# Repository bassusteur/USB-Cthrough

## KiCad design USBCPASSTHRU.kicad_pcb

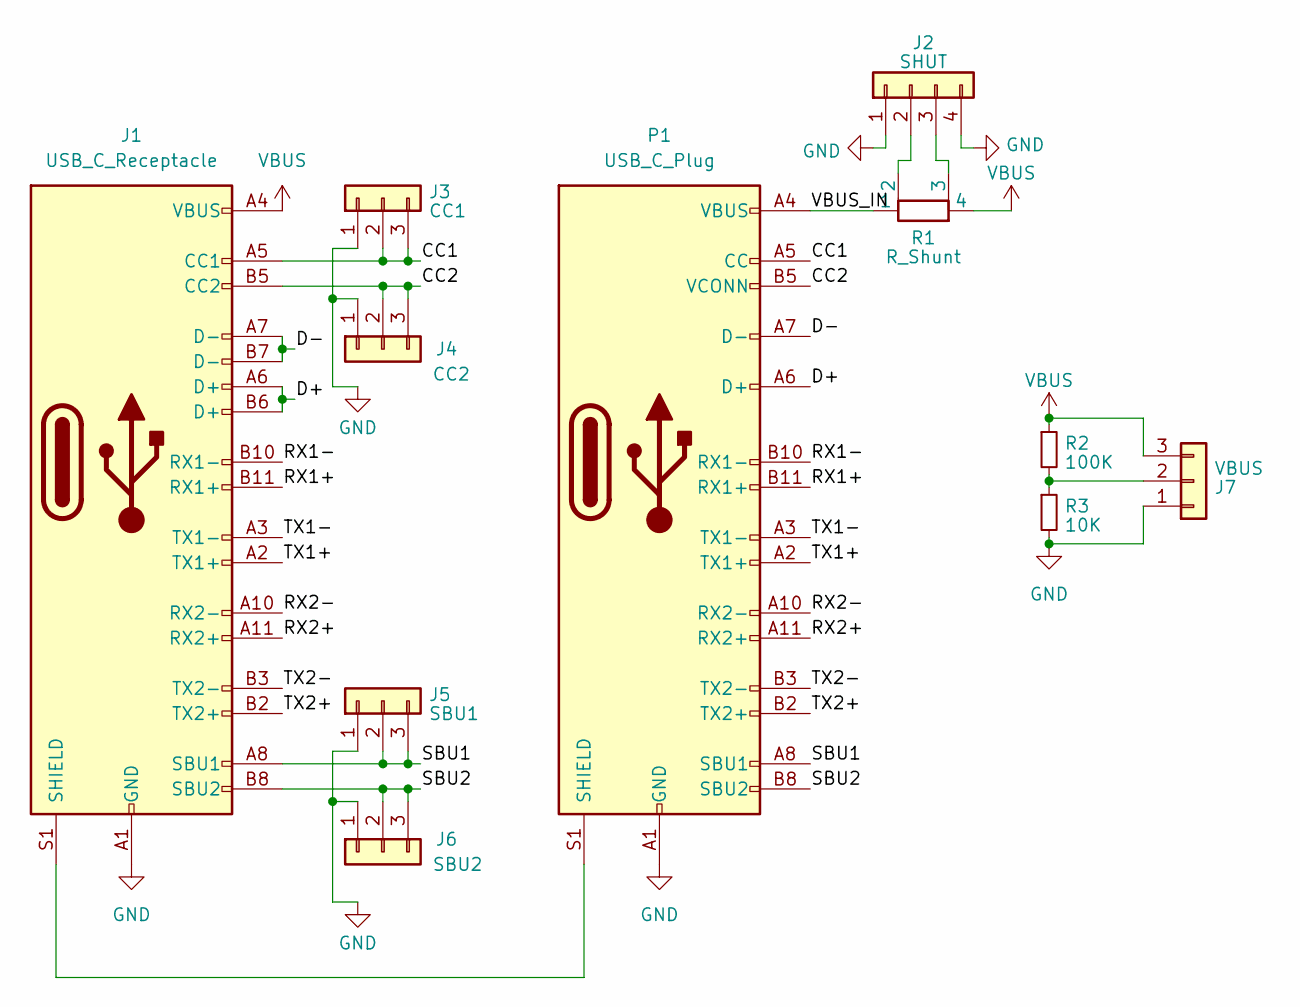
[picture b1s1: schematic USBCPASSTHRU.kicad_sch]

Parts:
J1: USB_C_Receptacle; USB_C_Receptacle_Amphenol_12401548E4-2A
J2: SHUT; PinHeader_1x04_P2.54mm_Vertical
J3: CC1; PinHeader_1x03_P2.54mm_Vertical
J4: CC2; PinHeader_1x03_P2.54mm_Vertical
J5: SBU1; PinHeader_1x03_P2.54mm_Vertical
J6: SBU2; PinHeader_1x03_P2.54mm_Vertical
J7: VBUS; PinHeader_1x03_P2.54mm_Vertical
P1: USB_C_Plug; USB_C_Plug_Molex_105444
R1: R_Shunt; Shunt
R2: 100K; R_0603_1608Metric
R3: 10K; R_0603_1608Metric

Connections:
/CC1: J1.A5 (CC1), J3.2, J3.3, P1.A5 (CC)
/CC2: J1.B5 (CC2), J4.2, J4.3, P1.B5 (VCONN)
/D+: J1.A6 (D+), J1.B6 (D+), P1.A6 (D+)
/D-: J1.A7 (D-), J1.B7 (D-), P1.A7 (D-)
/RX1+: J1.B11 (RX1+), P1.B11 (RX1+)
/RX1-: J1.B10 (RX1-), P1.B10 (RX1-)
/RX2+: J1.A11 (RX2+), P1.A11 (RX2+)
/RX2-: J1.A10 (RX2-), P1.A10 (RX2-)
/SBU1: J1.A8 (SBU1), J5.2, J5.3, P1.A8 (SBU1)
/SBU2: J1.B8 (SBU2), J6.2, J6.3, P1.B8 (SBU2)
/TX1+: J1.A2 (TX1+), P1.A2 (TX1+)
/TX1-: J1.A3 (TX1-), P1.A3 (TX1-)
/TX2+: J1.B2 (TX2+), P1.B2 (TX2+)
/TX2-: J1.B3 (TX2-), P1.B3 (TX2-)
/VBUS_IN: P1.A4 (VBUS), P1.A9 (VBUS), P1.B4 (VBUS), P1.B9 (VBUS), R1.1
GND: J1.A1 (GND), J1.A12 (GND), J1.B1 (GND), J1.B12 (GND), J2.1, J2.4, J3.1, J4.1, J5.1, J6.1, J7.1, P1.A1 (GND), P1.A12 (GND), P1.B1 (GND), P1.B12 (GND), R3.2
unnamed: J1.S1 (SHIELD), P1.S1 (SHIELD)
unnamed: J2.2, R1.2
unnamed: J2.3, R1.3
unnamed: J7.2, R2.2, R3.1
VBUS: J1.A4 (VBUS), J1.A9 (VBUS), J1.B4 (VBUS), J1.B9 (VBUS), J7.3, R1.4, R2.1

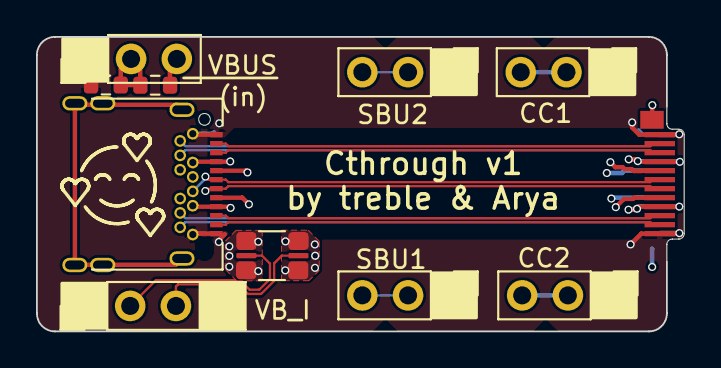
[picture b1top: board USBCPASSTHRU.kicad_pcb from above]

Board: 6 copper layers, 36.0 x 16.4 mm, 11 parts (0 on the bottom side), 21 nets.

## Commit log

2024-07-19 add GPL
